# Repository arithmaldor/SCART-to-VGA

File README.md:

# SCART to VGA
Adapt SCART to VGA (RGBS) with optional sync stripper. You can either include all the parts and select on and off with the switch, or leave the sync stripper circuit off entirely and just connect the center leg of the switch with the leg nearest the "Bypass" text.

# License
Licensed under CERN OHL 1.2.

# Thanks
Thanks to Beyond Pixels (@ChristianBruyer) for the request/suggestion.

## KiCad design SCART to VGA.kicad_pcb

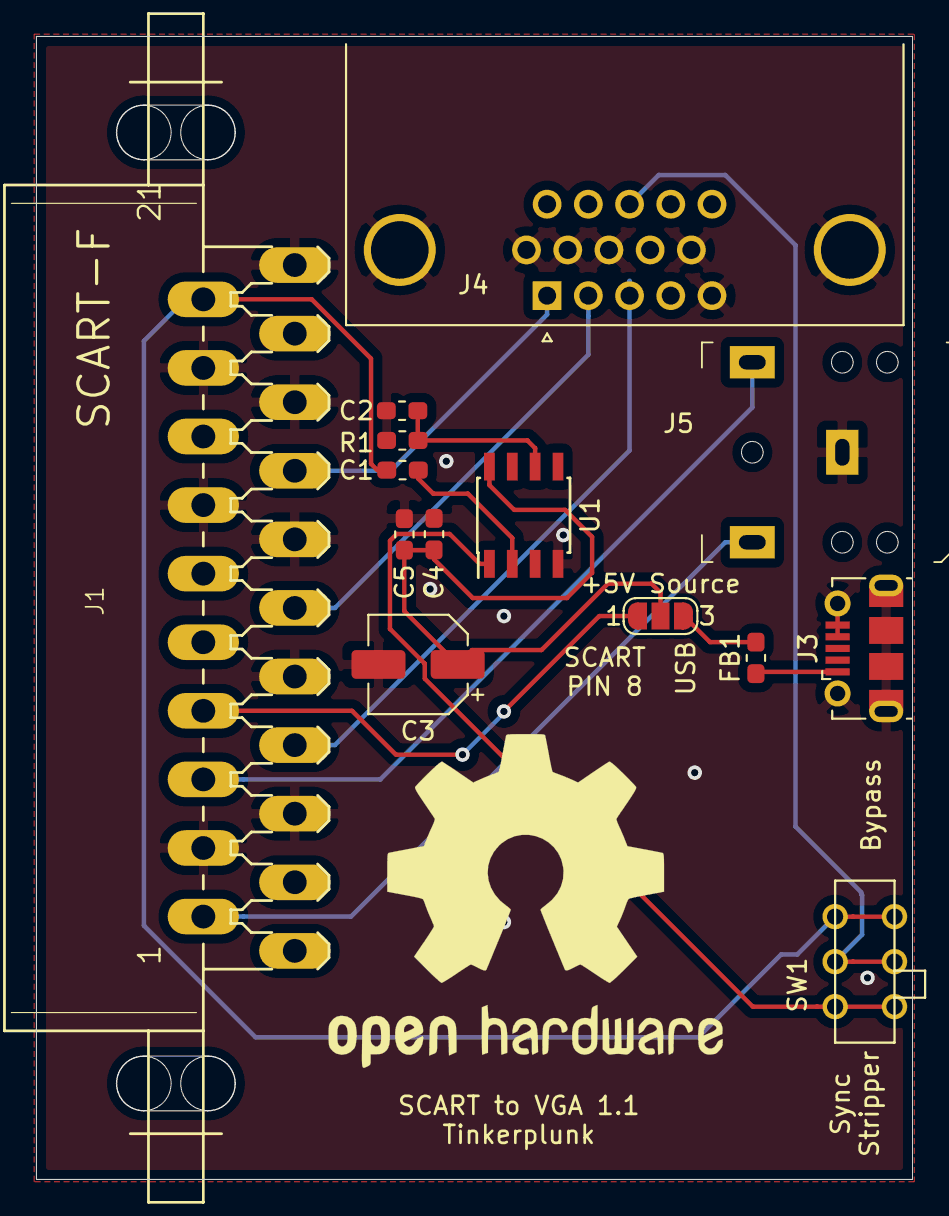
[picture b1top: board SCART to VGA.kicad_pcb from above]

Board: 2 copper layers, 48.7 x 63.5 mm, 14 parts (0 on the bottom side), 14 nets.

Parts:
+5V Source: SolderJumper_3_Bridged12; SolderJumper-3_P1.3mm_Open_RoundedPad1.0x1.5mm_NumberLabels
C1, C2, C4: 100nF; C_0603_1608Metric_Pad1.05x0.95mm_HandSolder
C3: 10uF; CP_Elec_5x5.3
C5: 10nF; C_0603_1608Metric_Pad1.05x0.95mm_HandSolder
FB1: 220OHM; L_0603_1608Metric_Pad1.05x0.95mm_HandSolder
J1: SCART-F
J3: USB_B_Micro; USB_Micro-B_Molex-105017-0001
J4: DB15_Female_HighDensity; VGA
J5: AudioJack3; Headphone_Jack_3.5mm_SJ1-3523N
R1: 680K; R_0603_1608Metric_Pad1.05x0.95mm_HandSolder
SW1: Conn_01x03_Male; DPDT
U1: LM1881; SOIC-8_3.9x4.9mm_P1.27mm

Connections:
BLUE: J1.7, J4.3
GND: C2.2, C3.2, C4.1, C5.1, J1.4, J1.5, J1.9, J1.13, J1.14, J1.17, J1.18, J1.21, J3.4, J3.5, J3.6, J4.0, J4.5, J4.6, J4.7, J4.8, J4.10, J5.S, R1.2, U1.4
GREEN: J1.11, J4.2
LEFT: J1.6, J5.T
unnamed: C1.1, U1.2
unnamed: C2.1, R1.1, U1.6
unnamed: +5V Source.2, C3.1, C4.2, C5.2, U1.8
unnamed: FB1.1, J3.1
unnamed: +5V Source.1, J1.8
unnamed: SW1.1, SW1.4, U1.1
RED: J1.15, J4.1
RIGHT: J1.2, J5.R
SYNC_IN: C1.2, J1.20, SW1.3, SW1.6
SYNC_OUT: J4.13, SW1.2, SW1.5

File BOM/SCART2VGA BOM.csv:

Qty,Ref(s),Value,Footprint,Description,Note,Digikey,Arrow,LCSC,Other,
1,C5,10nF,0603,Ceramic 50V,,https://www.digikey.com/product-detail/en/samsung-electro-me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,https://www.arrow.com/en/products/cc0603krx7r9bb103/yageo,https://lcsc.com/product-detail/Others_Samsung-Electro-Mecha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,,
3,"C1, C2, C4",100nF,0603,Ceramic 50V,,https://www.digikey.com/product-detail/en/CL10F104ZO8NNNC/12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,https://www.arrow.com/en/products/cl10f104zo8nnnc/samsung-el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,https://lcsc.com/product-detail/Multilayer-Ceramic-Capacitor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,,
1,C3,10uF,4x5.4,Elec. 25V,,https://www.digikey.com/product-detail/en/panasonic-electron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,https://www.arrow.com/en/products/eeefk1e100r/panasonic,https://lcsc.com/product-detail/Others_PANASONIC-EEE1EA100WA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,,
1,R1,680K,0603,1%,,https://www.digikey.com/product-detail/en/vishay-beyschlag/M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,https://www.arrow.com/en/products/mct06030c6803fp500/vishay,,,
1,FB1,220R,0603,Ferrite Bead,,https://www.digikey.com/product-detail/en/tdk-corporation/MP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,https://www.arrow.com/en/products/mpz1608s221ata00/tdk,https://lcsc.com/product-detail/Ferrite-Beads-And-Chips_TDK_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,,
1,U1,LM1881,SOIC-8,,,https://www.digikey.com/product-detail/en/texas-instruments/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,https://www.arrow.com/en/products/lm1881mxnopb/texas-instruments,https://lcsc.com/product-detail/Interface-Specialized_HGSEMI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,, 
1,J1,SCART,Right Angle,,,,,,https://console5.com/store/female-scart-jp21-through-hole-pc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,
1,J3,microUSB,Right Angle,Molex Style,,https://www.digikey.com/product-detail/en/molex/1050170001/W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,https://www.arrow.com/en/products/1050170001/molex,https://lcsc.com/product-detail/USB-Connectors_Jing-Extensio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,,
1,J4,VGA,Right Angle,Female,,https://www.digikey.com/product-detail/en/amphenol-icc-fci/I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,https://www.arrow.com/en/products/icd15s13e4gx00lf/amphenol-fci,https://lcsc.com/product-detail/D-Sub-Connectors_BOOMELE-Boo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,,
1,J5,3.5mm,Right Angle,Headphone,SJ1-3523NG,https://www.digikey.com/products/en?keywords=SJ1-3523NG,https://www.arrow.com/en/products/sj1-3523ng/cui-inc,https://lcsc.com/product-detail/Audio-Video-Connectors_BOOME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,,
1,SW1,DPDT,THT RA,,,https://www.digikey.com/product-detail/en/c-k/JS202011AQN/40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,https://www.arrow.com/en/products/js202011aqn/ck,https://lcsc.com/product-detail/Toggle-Switches_C-K_JS202011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,,

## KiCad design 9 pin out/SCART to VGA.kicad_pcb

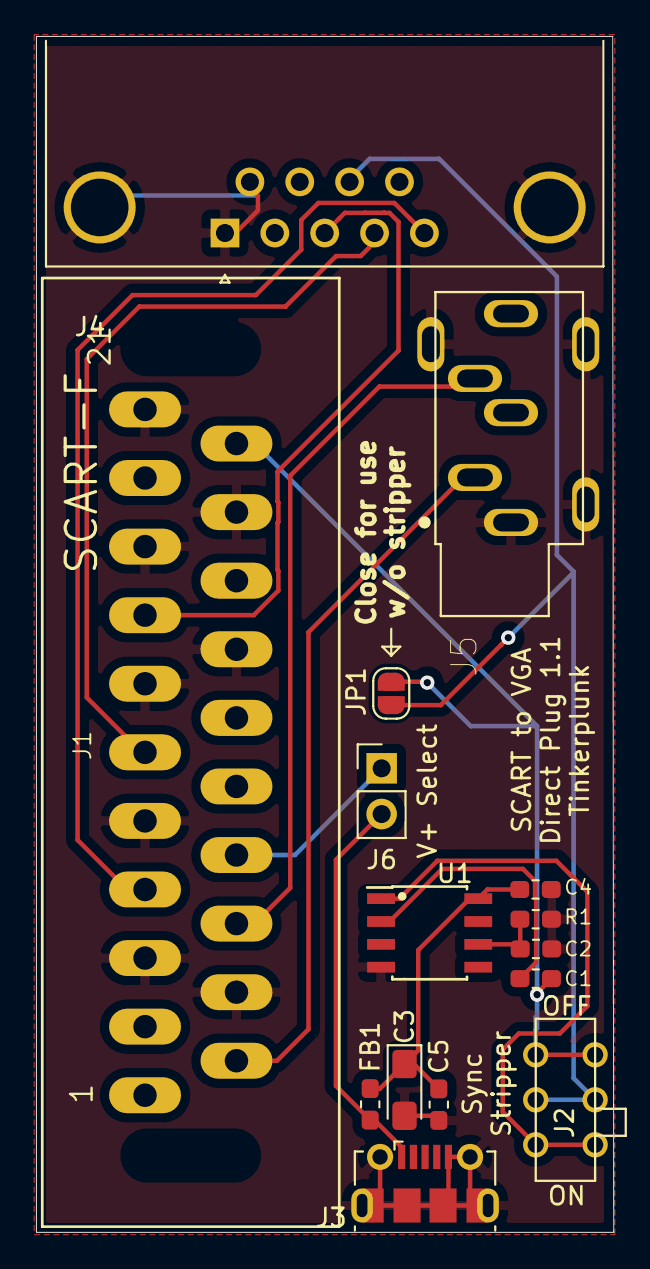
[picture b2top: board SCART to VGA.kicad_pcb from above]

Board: 2 copper layers, 32.1 x 66.4 mm, 15 parts (0 on the bottom side), 14 nets.

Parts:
C1, C2, C4: 100nF; C_0603_1608Metric_Pad1.05x0.95mm_HandSolder
C3: 10uF; CP_EIA-3216-18_Kemet-A_Pad1.58x1.35mm_HandSolder
C5: 10nF; C_0603_1608Metric_Pad1.05x0.95mm_HandSolder
FB1: 220OHM; L_0603_1608Metric_Pad1.05x0.95mm_HandSolder
J1: SCART-F; SCART_F
J2: Conn_01x03_Male; JS202011
J3: USB_B_Micro; USB_Micro-B_Molex-105017-0001
J4: DB15_Female_HighDensity; DSUB-9_Female_Horizontal_P2.77x2.84mm_EdgePinOffset9.90mm_H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
J5: AudioJack3; CUI_SJ1-3533NG
J6: V+ Select; PinHeader_1x02_P2.54mm_Vertical
JP1: SolderJumper-2_P1.3mm_Open_RoundedPad1.0x1.5mm
R1: 680K; R_0603_1608Metric_Pad1.05x0.95mm_HandSolder
U1: LM1881; SOIC-8_3.9x4.9mm_P1.27mm

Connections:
BLUE: J1.7, J4.5
GND: C2.2, C3.2, C4.1, C5.1, J1.4, J1.5, J1.9, J1.13, J1.14, J1.17, J1.18, J1.21, J3.5, J3.6, J4.0, J4.1, J5.S, R1.2, U1.4
GREEN: J1.11, J4.4
LEFT: J1.6, J5.T
unnamed: C1.1, U1.2
unnamed: C2.1, R1.1, U1.6
unnamed: C3.1, C4.2, C5.2, FB1.2, U1.8
unnamed: J1.8, J6.1
unnamed: J2.1, J2.4, U1.1
RED: J1.15, J4.3
RIGHT: J1.2, J5.R
SCART_VOLTAGE: FB1.1, J3.1, J6.2
SYNC_IN: C1.2, J1.20, J2.3, J2.6, JP1.2
SYNC_OUT: J2.2, J2.5, J4.8, JP1.1

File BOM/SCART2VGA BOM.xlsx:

Qty | Ref(s) | Value | Footprint | Description | Note | Digikey | Arrow | LCSC | Other
1 | C5 | 10nF | 0603 | Ceramic 50V |  | https://www.digikey.com/product-detail/en/samsung-electro-me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 | https://www.arrow.com/en/products/cc0603krx7r9bb103/yageo | https://lcsc.com/product-detail/Others_Samsung-Electro-Mecha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
3 | C1, C2, C4 | 100nF | 0603 | Ceramic 50V |  | https://www.digikey.com/product-detail/en/CL10F104ZO8NNNC/12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 | https://www.arrow.com/en/products/cl10f104zo8nnnc/samsung-el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 | https://lcsc.com/product-detail/Multilayer-Ceramic-Capacitor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
1 | C3 | 10uF | 4x5.4 | Elec. 25V |  | https://www.digikey.com/product-detail/en/panasonic-electron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 | https://www.arrow.com/en/products/eeefk1e100r/panasonic | https://lcsc.com/product-detail/Others_PANASONIC-EEE1EA100WA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
1 | R1 | 680K | 0603 | 0.01 |  | https://www.digikey.com/product-detail/en/vishay-beyschlag/M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 | https://www.arrow.com/en/products/mct06030c6803fp500/vishay
1 | FB1 | 220R | 0603 | Ferrite Bead |  | https://www.digikey.com/product-detail/en/tdk-corporation/MP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 | https://www.arrow.com/en/products/mpz1608s221ata00/tdk | https://lcsc.com/product-detail/Ferrite-Beads-And-Chips_TDK_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
1 | U1 | LM1881 | SOIC-8 |  |  | https://www.digikey.com/product-detail/en/texas-instruments/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 | https://www.arrow.com/en/products/lm1881mxnopb/texas-instruments | https://lcsc.com/product-detail/Interface-Specialized_HGSEMI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
1 | J1 | SCART | Right Angle |  |  |  |  |  | https://console5.com/store/female-scart-jp21-through-hole-pc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
1 | J3 | microUSB | Right Angle | Molex Style |  | https://www.digikey.com/product-detail/en/molex/1050170001/W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 | https://www.arrow.com/en/products/1050170001/molex | https://lcsc.com/product-detail/USB-Connectors_Jing-Extensio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
1 | J4 | VGA | Right Angle | Female |  | https://www.digikey.com/product-detail/en/amphenol-icc-fci/I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 | https://www.arrow.com/en/products/icd15s13e4gx00lf/amphenol-fci | https://lcsc.com/product-detail/D-Sub-Connectors_BOOMELE-Boo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
1 | J5 | 3.5mm | Right Angle | Headphone | SJ1-3523NG | https://www.digikey.com/products/en?keywords=SJ1-3523NG | https://www.arrow.com/en/products/sj1-3523ng/cui-inc | https://lcsc.com/product-detail/Audio-Video-Connectors_BOOME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
1 | SW1 | DPDT | THT RA |  |  | https://www.digikey.com/product-detail/en/c-k/JS202011AQN/40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 | https://www.arrow.com/en/products/js202011aqn/ck | https://lcsc.com/product-detail/Toggle-Switches_C-K_JS202011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

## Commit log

2019-04-23 Added License File
2019-04-23 renamed gerber file
2019-04-23 Trace movement
    slightly moved some traces farther away from the SCART through holes
2019-04-26 Created branch
    Branch where the SCART head lays on top of the PCB for direct plug in with a male hd-15 port.
2019-04-28 1.1 Update
    Moved things around, made cutout for headphone jack, changed headphone jack part, added jumper for getting voltage optionally from the SCART socket.
2019-05-30 Direct Plug
    Male VGA with vertical SCART connector for minimum horizontal footprint. Allows direct connection of SCART to VGA switchboxes such as Extron units, though only on the top row.
2019-05-31 changed name of gerber zip
2019-06-17 fixed routing for bypass cap
    Fixed routing for LM1881 bypass cap so voltage input hits the cap first.
2019-06-25 replaced and rotated headphone jack
2019-06-25 recovery
2019-06-25 added jumper to make it easier to use without sync stripper
2019-07-31 fixed BOM
2019-07-31 saving
2019-10-24 9 pin version added
    for extron rgb 202 rxi
2020-07-02 Closed all open issues
    1. added jumper for voltage source
    2. changed pin headers to 2 row dpdt switch
    3. Changed VGA to correct footprint
    4. Fixed placement of headphone jack
    5. Converted BOM to csv
    6. updated license file.
2020-07-02 added new renders folder
